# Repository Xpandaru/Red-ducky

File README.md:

# Red-ducky

 In this project I'll make my own Rubber Ducky, named Red ducky ! A Rubber Ducky is a hacking tool that mimics a keyboard to inject a sequence of keys. I started this project with no knowledge of PCB design, so it promises to be very educational.

## The story of the project

It all started when a friend introduced me to [Hack Club](https://hackclub.com/) during the [Cyber ​​Ninja CTF](https://www.cyber-ninja-ctf.fr/) (a cybersecurity competition organized by [Oteria Cyber ​​School](https://www.oteria.fr/)). I was quickly drawn to the [Blueprint program](https://blueprint.hackclub.com) because I knew absolutely nothing about electronics, and being very curious, I saw it as the perfect opportunity to explore the field. I soon had the idea to recreate a Rubber Ducky (a very popular cybersecurity tool) to understand how it worked and have my own by the end of the project. From there, I began learning all the necessary knowledge and developing my project based on the [custom devboard](https://blueprint.hackclub.com/starter-projects/devboard) guided project.

## Some screenshots

### The PCB :

### The schematic :

# How to build

## Ordering the PCB from JLCPCB

[JLCPCB](https://jlcpcb.com/) is a company that offers fast and affordable PCB manufacturing and assembly services through an easy-to-use online platform.

First, go to the [JLCPCB](https://jlcpcb.com/) website and start a new order by clicking the “Order Now” button in the top-right corner. Then, upload the [PRODUCTION.zip](https://github.com/Xpandaru/Red-ducky/blob/main/PCB/PRODUCTION/PRODUCTION.zip) file in the “Add Gerber File” field. You don’t need to change any settings except “PCB Qty” to select how many Red-Ducky boards you want. At the very bottom, enable “PCB Assembly”; again, you don’t need to change any settings. Finally, click “Next” on the right side of the screen under “Calculated Price.” Once that’s done, click “Next” again to reach the “Bill of Materials” tab, and upload the [BOM.csv](https://github.com/Xpandaru/Red-ducky/blob/main/PCB/PRODUCTION/BOM.csv) and [CPL.csv](https://github.com/Xpandaru/Red-ducky/blob/main/PCB/PRODUCTION/CPL.csv) files available in the repository.

Then click “Process BOM & CPL”, and you will see the list of components appear. However, you will likely notice that component **J1** shows an error in the “Select” column labeled “Standard Only.” This happens because the “PCBA Type” setting is still set to “Economic.” To fix this, you have two options : either click “Standard Only” and then “Switch to Standard PCBA” (which will increase the price), or click “Next” and choose “Do not place” in each popup, which will remove the component from the assembly. If you choose the second option, you will need to purchase the part separately (for example from [LCSC](https://www.lcsc.com/product-detail/C2765195.html)) and solder it yourself.

After that, you will see a preview of the components placed on the PCB, just make sure that the placement matches the image below and you can simply click “Next” and follow the instructions to complete your assembled PCB order.

## Building the Red-Ducky

Once you have received all the parts, solder **J1** if you ordered it separately. Otherwise, you just need to 3D print the [case](https://github.com/Xpandaru/Red-ducky/tree/main/CAD) available in the repository (I haven’t had the chance to print it yet, so I’m not sure if it works) and place the fully assembled Red-Ducky inside !

Finally, you can simply follow the tutorials in the [wiki](https://github.com/Xpandaru/Red-ducky/wiki) to flash the firmware and start using your Red-Ducky.

# Bill of materials

| Item | Description | Quantity | Unit price (\$) | Total prince (\$) | URL |
| --- | --- | ---: | ---: | ---: | --- |
| 0402CG330J500NT | 33pF 50V C0G ±5% 0402 Multilayer Ceramic Capacitors MLCC - SMD/SMT ROHS | 4   | 0.001 | 0.004 | https://jlcpcb.com/partdetail/1914-0402CG330J500NT/C1562 |
| DSX321G 12MHz | SMD3225-4P Crystals ROHS | 5   | 0.4003 | 2.0015 | https://jlcpcb.com/partdetail/KDSDaishinku-DSX321G12MHz/C93234 |
| KT-0603W | 100mW 120° 2.6V~3.1V 360mcd 5mA Discrete Diode White Yellow Lens op View Mount 0603 LED Indication - Discrete ROHS | 2   | 0.0104 | 0.0208 | https://jlcpcb.com/partdetail/Hubei_KENTOElec-KT0603W/C2290 |
| CL05A105KA5NQNC | 1uF 25V X5R ±10% 0402 Multilayer Ceramic Capacitors MLCC - SMD/SMT ROHS | 4   | 0.0029 | 0.0116 | https://jlcpcb.com/partdetail/53938-CL05A105KA5NQNC/C52923 |
| RP2040 | 12bit 133MHz 30 LQFN-56(7x7) Microcontrollers (MCU/MPU/SOC) ROHS | 2   | 0.9298 | 1.8596 | https://jlcpcb.com/partdetail/RaspberryPi-RP2040/C2040 |
| 0402WGF1001TCE | \-55℃~+155℃ 1kΩ 50V 62.5mW Thick Film Resistor ±1% ±100ppm/℃ 0402 Chip Resistor - Surface Mount ROHS | 6   | 0.0006 | 0.0036 | https://jlcpcb.com/partdetail/12256-0402WGF1001TCE/C11702 |
| W25Q16JVUXIQ | \-40℃~+85℃ 100,000 Cycles 10uA 133MHz 16Mbit 2.7V~3.6V 20 Years 3ms SPI USON-8-EP(2x3) NOR FLASH ROHS | 2   | 0.5448 | 1.0896 | https://jlcpcb.com/partdetail/WinbondElec-W25Q16JVUXIQ/C2843335 |
| CL05B104KO5NNNC | 100nF 16V X7R ±10% 0402 Multilayer Ceramic Capacitors MLCC - SMD/SMT ROHS | 22  | 0.0012 | 0.0264 | https://jlcpcb.com/partdetail/1877-CL05B104KO5NNNC/C1525 |
| 0402WGF1002TCE | \-55℃~+155℃ 10kΩ 50V 62.5mW Thick Film Resistor ±1% ±100ppm/℃ 0402 Chip Resistor - Surface Mount ROHS | 2   | 0.0005 | 0.001 | https://jlcpcb.com/partdetail/26487-0402WGF1002TCE/C25744 |
| CL10A106KP8NNNC | 10V 10uF X5R ±10% 0603 Multilayer Ceramic Capacitors MLCC - SMD/SMT ROHS | 4   | 0.0057 | 0.0228 | https://jlcpcb.com/partdetail/20411-CL10A106KP8NNNC/C19702 |
| 0402WGF220JTCE | \-55℃~+155℃ 22Ω 50V 62.5mW Thick Film Resistor ±1% ±100ppm/℃ 0402 Chip Resistor - Surface Mount ROHS | 4   | 0.0006 | 0.0024 | https://jlcpcb.com/partdetail/25835-0402WGF220JTCE/C25092 |
| MCP1700T-3302E/TT | IC REG LINEAR 3.3V 250MA SOT23-3 | 2   | 0.51 | 1.02 | https://www.lcsc.com/product-detail/C39051.html |
| MOLEX 48037-2200 | USB-A (USB TYPE-A) Receptacle Connector 4 Position Solder Cup | 2   | 2.0539 | 4.1078 | https://www.lcsc.com/product-detail/C2765195.html |
| SKRKAHE020 | SWITCH TACTILE SPST-NO 0.05A 12V | 2   | 0.41 | 0.82 | https://www.lcsc.com/product-detail/C202388.html |
| PCB | Green, 1.6 Thickness, HASL(with lead) | 5   | 0.4 | 2   |     |
| PCBA | Assemble top side | 2   | 12.875 | 25.75 |     |
| 3D printing | 3D printing of the case | 1   | 0.87 | 0.87 |     |

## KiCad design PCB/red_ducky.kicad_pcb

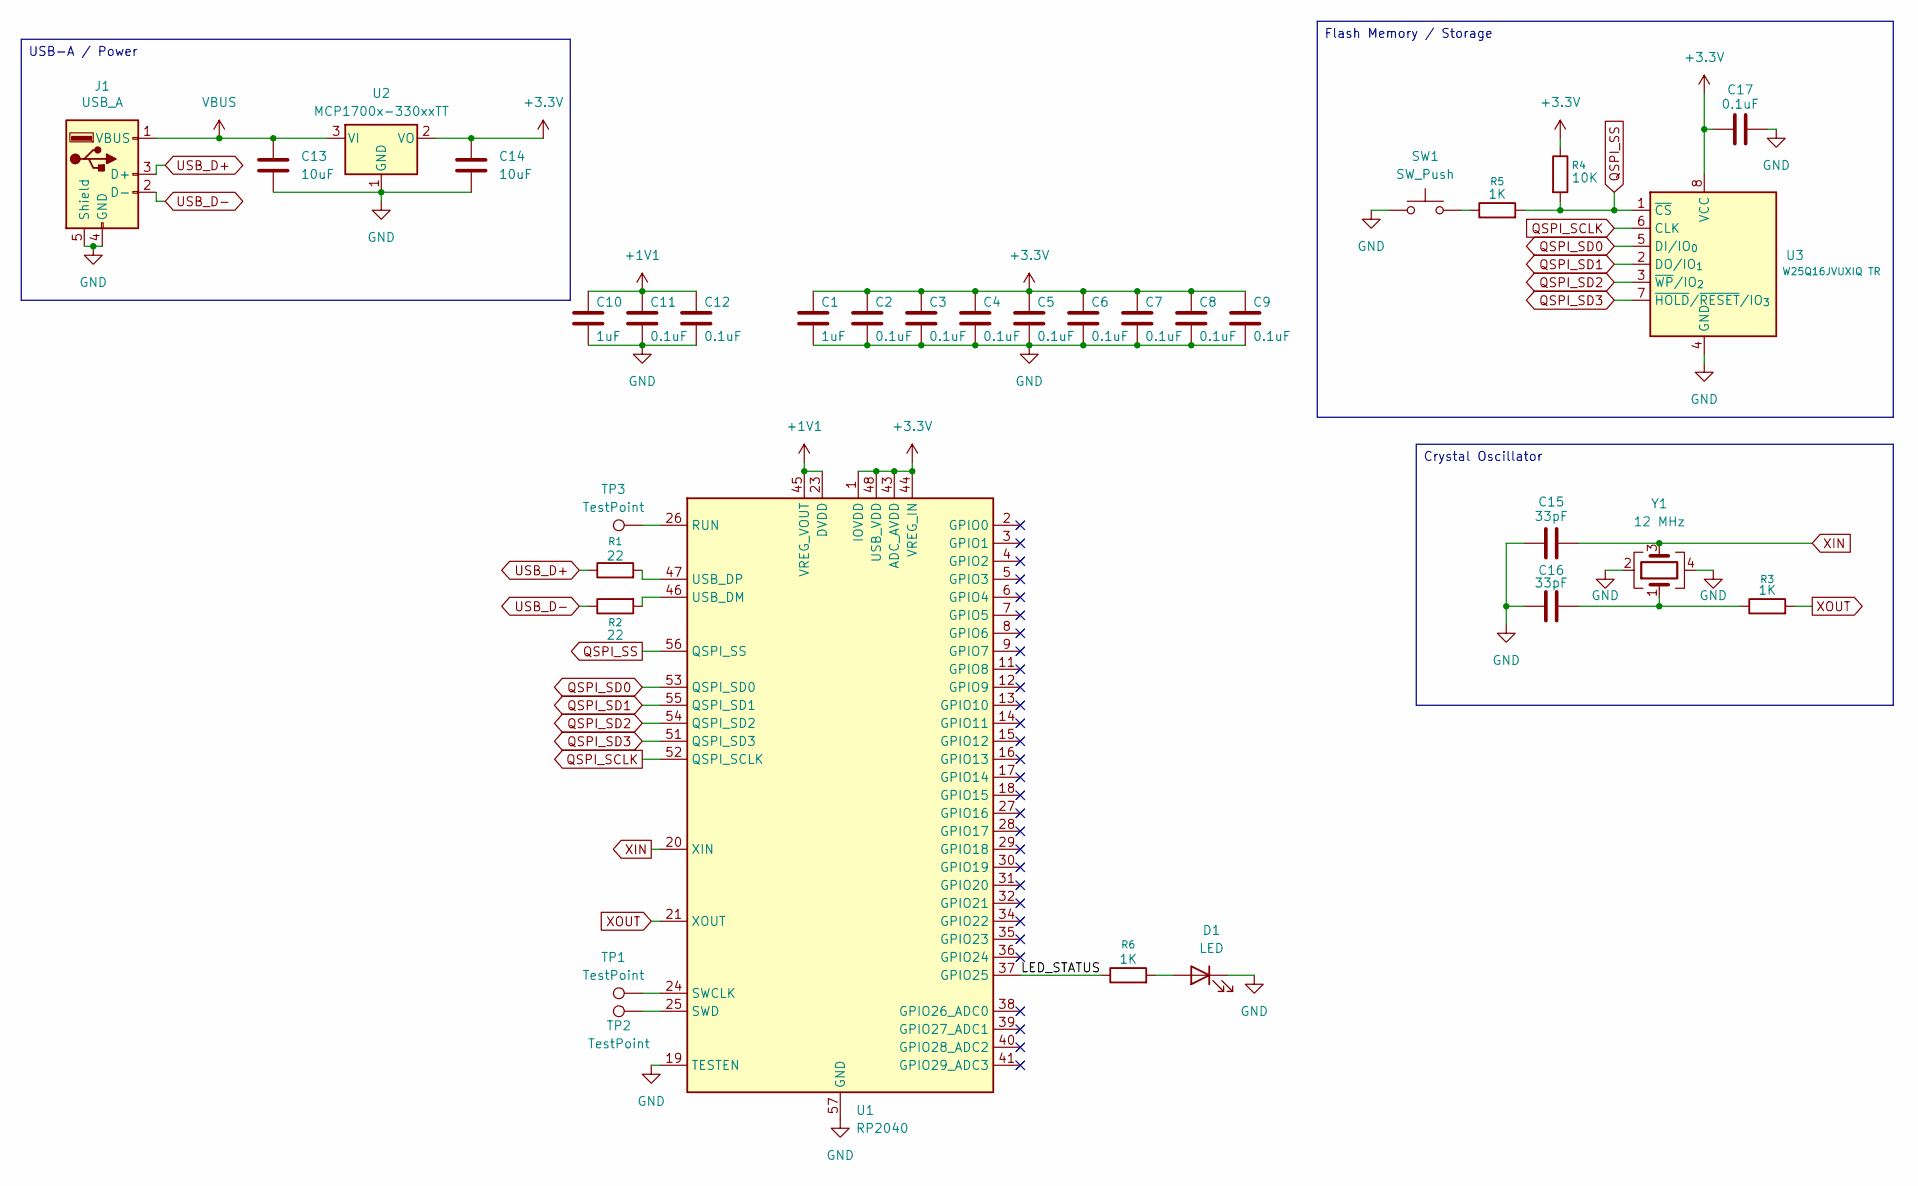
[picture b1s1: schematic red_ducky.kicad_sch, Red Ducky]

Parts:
C1, C10: 1uF; C_0402_1005Metric
C2, C3, C4, C5, C6, C7, C8, C9, C11, C12, C17: 0.1uF; C_0402_1005Metric
C13, C14: 10uF; C_0603_1608Metric
C15, C16: 33pF; C_0402_1005Metric
D1: LED; LED_0603_1608Metric
J1: USB_A; USB_A_CNCTech_1001-011-01101_Horizontal
R1, R2: 22; R_0402_1005Metric
R3, R5, R6: 1K; R_0402_1005Metric
R4: 10K; R_0402_1005Metric
SW1: SW_Push; SW_Push_SPST_NO_Alps_SKRK
TP1, TP2, TP3: TestPoint; TestPoint_Pad_1.5x1.5mm
U1: RP2040; QFN-56-1EP_7x7mm_P0.4mm_EP3.2x3.2mm
U2: MCP1700x-330xxTT; SOT-23
U3: W25Q16JVUXIQ TR; Winbond_USON-8-1EP_3x2mm_P0.5mm_EP0.2x1.6mm
Y1: 12 MHz; Crystal_SMD_3225-4Pin_3.2x2.5mm

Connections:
+1V1: C10.1, C11.1, C12.1, U1.23 (DVDD), U1.45 (VREG_VOUT), U1.50 (DVDD)
+3.3V: C1.1, C2.1, C3.1, C4.1, C5.1, C6.1, C7.1, C8.1, C9.1, C14.1, C17.1, R4.1, U1.1 (IOVDD), U1.10 (IOVDD), U1.22 (IOVDD), U1.33 (IOVDD), U1.42 (IOVDD), U1.43 (ADC_AVDD), U1.44 (VREG_IN), U1.48 (USB_VDD), U1.49 (IOVDD), U2.2 (VO), U3.8 (VCC)
/LED_STATUS: R6.1, U1.37 (GPIO25)
GND: C1.2, C2.2, C3.2, C4.2, C5.2, C6.2, C7.2, C8.2, C9.2, C10.2, C11.2, C12.2, C13.2, C14.2, C15.1, C16.1, C17.2, D1.1 (K), J1.4 (GND), J1.5 (Shield), SW1.1, U1.19 (TESTEN), U1.57 (GND), U2.1 (GND), U3.4 (GND), Y1.2, Y1.4
unnamed: C16.2, R3.1, Y1.1
unnamed: D1.2 (A), R6.2
unnamed: R5.1, SW1.2
unnamed: TP3.1, U1.26 (RUN)
unnamed: TP1.1, U1.24 (SWCLK)
unnamed: TP2.1, U1.25 (SWD)
unnamed: R2.2, U1.46 (USB_DM)
unnamed: R1.2, U1.47 (USB_DP)
QSPI_SCLK: U1.52 (QSPI_SCLK), U3.6 (CLK)
QSPI_SD0: U1.53 (QSPI_SD0), U3.5 (DI/IO_{0})
QSPI_SD1: U1.55 (QSPI_SD1), U3.2 (DO/IO_{1})
QSPI_SD2: U1.54 (QSPI_SD2), U3.3 (~WP/IO_{2})
QSPI_SD3: U1.51 (QSPI_SD3), U3.7 (~HOLD/~RESET/IO_{3})
QSPI_SS: R4.2, R5.2, U1.56 (QSPI_SS), U3.1 (~CS)
USB_D+: J1.3 (D+), R1.1
USB_D-: J1.2 (D-), R2.1
VBUS: C13.1, J1.1 (VBUS), U2.3 (VI)
XIN: C15.2, U1.20 (XIN), Y1.3
XOUT: R3.2, U1.21 (XOUT)

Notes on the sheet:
Crystal Oscillator
Flash Memory / Storage
USB-A / Power

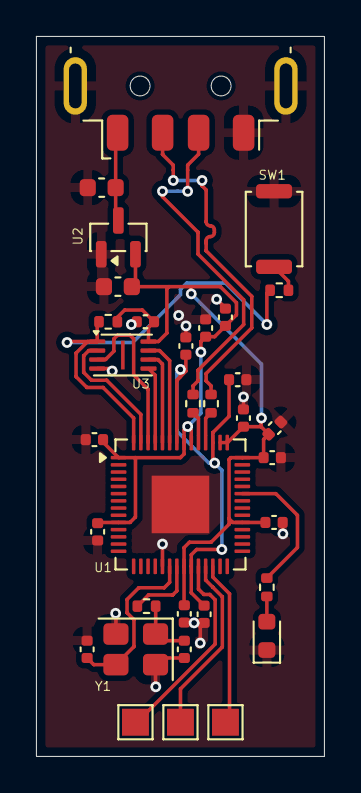
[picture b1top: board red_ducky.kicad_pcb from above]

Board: 2 copper layers, 16.0 x 40.0 mm, 33 parts (0 on the bottom side), 23 nets.

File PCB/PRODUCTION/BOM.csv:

Designator,Footprint,Quantity,Value,LCSC Part #
"C1, C10",402,2,1uF,C52923
"C11, C12, C17, C2, C3, C4, C5, C6, C7, C8, C9",402,11,0.1uF,C1525
"C13, C14",603,2,10uF,C19702
"C15, C16",402,2,33pF,C1562
D1,603,1,LED,C2290
J1,USB_A_Molex_48037-2200_Horizontal,1,USB_A,C2765195
"R1, R2",402,2,22,C25092
"R3, R5, R6",402,3,1K,C11702
R4,402,1,10K,C25744
SW1,SW_Push_SPST_NO_Alps_SKRK,1,SW_Push,C202388
U1,QFN-56-1EP_7x7mm_P0.4mm_EP3.2x3.2mm,1,RP2040,C2040
U2,SOT-23,1,MCP1700x-330xxTT,C39051
U3,Winbond_USON-8-1EP_3x2mm_P0.5mm_EP0.2x1.6mm,1,W25Q16JVUXIQ TR,C2843335
Y1,Crystal_SMD_3225-4Pin_3.2x2.5mm,1,12 MHz,C93234

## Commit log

2025-12-20 Expand README with project details and materials
    Added detailed project description, story, screenshots, and bill of materials.
2025-12-20 Add journal entries for PCB project progress
    Added a detailed journal documenting the progress of the project.
2025-12-20 Create
2025-12-20 Create test
2025-12-20 Adding .step file
2025-12-20 Adding the case 3D model
2025-12-20 Creating new folder
2025-12-20 Adding 3D render
2025-12-20 Adding Kicad files
2025-12-20 Adding zipped gerbers
2025-12-20 Adding PCB 3D model
2025-12-20 Adding the PCB 3D model
2025-12-21 Revise bill of materials format and details
    Updated the bill of materials
2025-12-21 Adding the BOM
2025-12-21 Update journal
2025-12-22 Create Firmware folder
2025-12-22 Add CMakeLists.txt
2025-12-22 Add Dependencies.txt
2025-12-22 Adding an entry in the journal
2025-12-26 Updated BOM
2026-01-14 Update USB connector details in README
2026-01-14 Add updated kicad files
2026-01-14 Adding updated PRODUCTION.zip
2026-01-14 Adding updated red_ducky.wrl
2026-02-25 Adding new journal entries
2026-02-25 Update total time spent in JOURNAL.md
    Updated total time spent in the journal to reflect new hours.
2026-02-26 Adding a new journal entry
2026-02-27 Adding journal entry
2026-02-27 New journal entry
2026-02-28 Updating CMakeLists.txt
2026-02-28 Updating main.c
2026-02-28 Updating usb_descriptors.c
2026-02-28 Updating the firmware
2026-03-05 Adding the day 14 entry
2026-03-05 Updating layout.c
2026-03-05 Updating layout.h
2026-03-05 Updating parser.c
2026-03-05 Updating parser.h
2026-03-06 Adding the day 15 journal entry
2026-03-07 Adding the day 16 journal entry
2026-03-07 Updating tusb_config.h
2026-03-07 Adding the compiled firmware
2026-03-07 Adding errors
2026-03-07 Upadting parser.c for errors
2026-03-07 Adding a 2nd day 16 entry
2026-03-19 Added LAYOUT command as a DELAY exception
2026-03-19 Updated the build
2026-03-28 Fix PICO_SDK_PATH variable usage in CMakeLists
2026-03-28 Updated main.c
2026-03-28 Patching GBDELAY 0 error
2026-03-28 Updating the builded firmware
2026-04-04 Create PRODUCTION folder
2026-04-04 Adding production files
2026-04-04 Update README with build instructions
2026-04-04 Updating CPL.csv
2026-04-04 Revise README
2026-05-10 Increased typing speed
2026-05-10 Updating the build file to type faster
